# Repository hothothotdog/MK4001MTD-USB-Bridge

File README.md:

This repository has moved to [https://codeberg.org/hothothotdog/MK4001MTD-USB-Bridge](https://codeberg.org/hothothotdog/MK4001MTD-USB-Bridge)

This GitHub copy is a frozen archive. New commits, issues, and pull requests should go to Codeberg.

---

Budget friendly changes to the PCB. Modified the PCB from 4-layers and 11cm long (about $70) to under 10cm and 2-layers which puts this in the $5 cost range at jlcpcb 

Schematic changes:
   - TLV62569DBV 
   Filter caps changed to higher value (as per datasheet recommendation)
   Voltage divider changed from 112K 25.3K (3.2v out) to sensible values 270K 60K (3.33v out)
   - Leds
   Current limiters set to 1mA (plenty bright enough)
   - Crystal 12MHz
   Changed 27pf caps to correct capacitance of 10pF each
   - NOR Flash
   Changed part to correct winbond W25Q16JVUXIQ
   Package changed to the correct DFN 3x2mm 

   new kicad files uploaded (27-4-2026) + ibom + images + pdf
   
# MK4001MTD USB Bridge

**RP2040 Pico firmware that bridges a Toshiba MK4001MTD 0.85" SDIO microdrive as a USB Mass Storage device.**

The MK4001MTD is a 4 GB Microdrive originally used in the Nokia N91 music phone and some other devices, like MP3 players or USB drives, back when flash storage was still quite expensive.

You might have seen introductions claiming this drive uses the MMC protocol, but that’s actually incorrect. I’ve been investigating this for a while: I tried building an 8-bit MMCplus card reader and tested different SD/MMC readers without success. As a last resort, I bought a Nokia N91 to capture logic traces and confirm what protocol it actually uses.

Here is the photo when I was trying to use it with my 8bit-MMCPlus reader board, and it turns out it is not MMC :(

So I end up getting N91 to collect traces:

Unlike standard ATA/CF Microdrives, it uses an SDIO interface with ATA commands tunneled through CMD52/CMD53. No existing driver supports this protocol, so this firmware implements the full stack from scratch.

This surprised me, because there is an SDIO-to-ATA standard called CE-ATA. But if you look closely at the release timeline, CE-ATA came later than this drive. As a result, this drive relies entirely on SDIO commands, and CE-ATA is not available. CE-ATA has two new cmd CMD60/CMD61 and utilize CMD12/39, but you can see from the traces it is not using any of those.  

The second hardware point to mention is that another piece of misinformation floating around—claiming it’s an 8-bit MMCPlus card—is not only untrue, but the pinout doesn’t follow the MMC standard either. You can find the Nokia N91 service manual with some documentation on the pinout: while the pin numbering follows the MMCPlus standard, the pin mapping does not. This is an important detail if you’re wiring it yourself: it uses the same MMC connector, but the pin mapping is different, more in the Hardware section.

Finally, note that this is co-developed with Claude/OpenClaw. I collected the logic traces manually and set up a closed-loop test station for OpenClaw to iterate on development—analyzing the traces and implementing features. The documentation will mostly be written by Claude; I’ll add my notes inline as well. I’ve also read and double-checked the documentation myself, and it should be reliable and easy to follow.

For insights into the analytics on N91 trace, it is under /docs/N91_TRACE_ANALYSIS.md, I've also put the N91 service manual there along with the raw logic traces.

See more in the blog post here: [https://www.willwhang.dev/Reading-MK4001MTD/](https://www.willwhang.dev/Reading-MK4001MTD/)  
See it in activity here: [https://youtu.be/GC4xil3_Bbc](https://youtu.be/GC4xil3_Bbc)

## Status

Fully functional USB mass storage with PIO-accelerated reads/writes and idle power management.

| Metric | Value |
|--------|-------|
| Read speed | 550 kB/s |
| Write speed | 364 kB/s |
| Capacity | 3.75 GB (7,862,400 sectors) |
| Filesystem | FAT32 verified (mount/unmount/fsck clean) |
| Data integrity | Write+readback MD5 verified |
| Idle standby | 1 second timeout → STANDBY IMMEDIATE |

## How It Works

### Architecture

```
USB Host ←→ USB MSC (TinyUSB) ←→ ATA Layer ←→ SDIO Layer (PIO) ←→ MK4001MTD
```

The firmware has four layers:

1. **USB MSC** (`msc_device.c`) — TinyUSB Mass Storage Class. Translates SCSI READ(10)/WRITE(10) into ATA sector operations. EP buffer is 8192 bytes, batching up to 16 sectors per USB transfer. Activity LEDs on GP9 (TX/write) and GP10 (RX/read). Tracks last I/O timestamp for idle power management.

2. **ATA-over-SDIO** (`ata_sdio.c`) — Implements ATA commands (IDENTIFY, READ SECTORS, WRITE SECTORS) by writing to ATA registers mapped into SDIO function 1 address space via CMD52, and transferring sector data via CMD53. 3-tier retry logic at CMD, data, and ATA levels.

3. **PIO SDIO** (`sdio_pio.c`, `sdio.pio`) — Hardware-accelerated SDIO using RP2040's PIO peripheral. Three PIO programs share a single state machine via dynamic program swapping:
   - **CMD tx/rx** (26 instructions) — sends SDIO commands and receives responses
   - **DAT read** (13 instructions) — reads data blocks from 4-bit DAT bus via DMA
   - **DAT write** (16 instructions) — writes data blocks to 4-bit DAT bus via DMA, with built-in CRC status reception and busy-wait

4. **Bit-bang SDIO** (`sdio_hw.c`) — Software SDIO used only for card initialization at 400 KHz (before PIO is set up). All runtime I/O uses PIO.

Human notes: Interestingly, Claude was really reluctant to implement SDIO in PIO, and a lot of development cycles were wasted bouncing back and forth between PIO and bit-banging.

### The SDIO-ATA Protocol

The MK4001MTD presents itself as an SDIO card with one I/O function. Standard SDIO card initialization (CMD5/CMD3/CMD7) sets up the bus, then ATA registers are accessed through SDIO commands:

**Register access (CMD52):** Each ATA register is mapped to a function 1 address:

| Address | Register | Usage |
|---------|----------|-------|
| 0x00 | DATA | CMD53 target for sector data |
| 0x01 | ERR/FEAT | Error (read) / Feature (write) |
| 0x02 | SECCOUNT | Sector count |
| 0x03 | LBA_LO | LBA bits 0-7 |
| 0x04 | LBA_MID | LBA bits 8-15 |
| 0x05 | LBA_HI | LBA bits 16-23 |
| 0x06 | DEV/HEAD | Device/Head + LBA bits 24-27 |
| 0x07 | CMD/STATUS | Command (write) / Status (read) |

**Data transfer (CMD53):** Sector data is transferred by issuing CMD53 in block mode targeting the DATA register (address 0x00). For multi-sector reads, a single CMD53 with `block_count=N` transfers N × 512 bytes in one SDIO multi-block transaction.

**Interrupt signaling:** The drive signals sector readiness by asserting an SDIO interrupt (INT_PENDING bit 1 in CCCR register 0x05). Reading the ATA STATUS register clears the interrupt.

### Read Path (Multi-Block PIO)

For a 16-sector read:

```
1. Write ATA registers via PIO CMD52:
     SECCOUNT=16, LBA_LO/MID/HI, DEV/HEAD=0xE0, CMD=0x20

2. Poll STATUS via CMD52 until DRQ (bit 3) is set

3. Swap PIO to DAT read program
4. Send CMD53: block_mode=1, fn=1, addr=0x0000, block_count=16

5. PIO DAT read: for each of the 16 blocks:
   a. Wait for start bit (all DAT lines low)
   b. DMA 1024 nibbles (512 bytes) from PIO RX FIFO to buffer
   c. Wait for SM to finish clocking CRC+end nibbles (poll SM PC)
   d. Repack nibbles → bytes in-place

6. Swap PIO back to CMD program
```

### Write Path (Multi-Block PIO)

For a 16-sector write:

```
1. Write ATA registers via PIO CMD52:
     SECCOUNT=16, LBA, DEV/HEAD=0xE0, CMD=0x30

2. Poll STATUS via CMD52 until DRQ (bit 3) is set
   (STATUS 0xD8 = BSY+DRQ treated as DRQ-ready, per N91 trace)

3. Swap PIO to DAT write program
4. Send CMD53: block_mode=1, fn=1, addr=0x0000, block_count=16

5. PIO DAT write: for each of the 16 blocks:
   a. Precompute CRC16-CCITT per DAT line (4 independent CRCs)
   b. Build nibble stream: start(0x0) + data(1024 nibbles) + CRC(16) + end(0xF)
   c. DMA nibble stream to PIO TX FIFO
   d. PIO clocks out all nibbles, then:
      - Switches DAT to input
      - Clocks 16 cycles for CRC status from card
      - Polls DAT0 until card releases busy
      - Fires IRQ 0 to signal block completion

6. Swap PIO back to CMD program
```

### PIO Program Swapping

The RP2040 PIO has 32 instruction slots per block. Our three programs total 55 instructions, so they can't coexist. Instead, a single SM0 on PIO0 is used, and programs are swapped by writing directly to PIO instruction memory:

```c
static void load_program_raw(const pio_program_t *program) {
    for (uint i = 0; i < program->length; i++)
        pio->instr_mem[FIXED_OFFSET + i] = program->instructions[i];
}
```

This bypasses the SDK's `pio_add_program`/`pio_remove_program` allocator. Program swap takes ~1 µs. Each swap is followed by a program-specific reinit that sets pin mappings, shift direction, and clock divider.

### Power Management

Analysis of Nokia N91 logic traces reveals aggressive power management:

- **Idle mode:** STANDBY IMMEDIATE (0xE0) every **~7.5 seconds**, even with no I/O. Each standby triggers full SDIO re-initialization (CMD5 retry → CMD3 → CMD7 → CCCR setup). 28 standby cycles observed in one idle session.
- **Active mode:** Standby issued between bursts of I/O (24 cycles during USB drive file operations).
- No other power commands (IDLE, SLEEP, CHECK POWER MODE) or CCCR power register accesses observed.

The firmware replicates this behavior with a configurable idle timeout:

```c
#define IDLE_STANDBY_MS 5000  // in main.c
```

Two paths trigger HDD power gating:

1. **Idle timeout** (5 seconds) — main loop detects no I/O activity
2. **USB suspend** — host suspends the USB port

Both paths send ATA STANDBY IMMEDIATE (0xE0) to flush the write cache and park heads, then cut power via GP9.

**Wake sequence** (triggered by first READ/WRITE after gate):
1. Power on HDD, wait 500ms for rail settling
2. PIO-based SDIO reinit: CMD5 (OCR) → 10ms settle → CMD3 (RCA) → CMD7 (select)
3. Switch to fast PIO clock, configure CCCR via CMD52 (4-bit bus, 512B blocks, fn1 enable)
4. Poll fn1 ready (CCCR IO_READY bit 1)
5. N91-style 30ms DRDY status poll until drive is ATA-ready

### Bad Sector Handling

When a multi-sector transfer hits a bad sector:
1. Chunk read fails → error recovery (IO_ABORT + fn1 reset, ~500ms)
2. Falls back to per-sector I/O to identify the failing block precisely
3. The ATA layer waits long enough to capture the final `STATUS/ERROR` bits instead of collapsing the failure into a generic `DRQ timeout`
4. Bad sector LBA cached → subsequent access fails quickly without re-hammering the drive
5. Any unrecovered block fails the SCSI command immediately with `MEDIUM ERROR`

On the known failing root-directory sector (`LBA 1952`), the drive now reports the real ATA result:

```text
READ: ST=0x51 ERR ERR=0x40 UNC LBA=1952
FAST-RD: ST=0x51 ERR ERR=0x40 UNC LBA=1952
```

## Building

### Prerequisites

- Raspberry Pi Pico SDK
- ARM toolchain (`arm-none-eabi-gcc`)
- CMake

### Build & Flash

```bash
cd /home/pi/mk4001_bridge/build
cmake ..
make -j4

sudo openocd -f interface/cmsis-dap.cfg -f target/rp2040.cfg \
  -c "adapter speed 1000" -c "init" -c "reset halt" -c "sleep 200" \
  -c "program /home/pi/mk4001_bridge/build/mk4001_bridge.elf verify" \
  -c "reset run" -c "exit"
```

### Hardware Wiring

| Pico GPIO | Function | Notes |
|-----------|----------|-------|
| GP2 | SDIO_CLK | Host clock output |
| GP3 | SDIO_CMD | Bidirectional command line |
| GP4 | SDIO_DAT0 | Data bit 0 |
| GP5 | SDIO_DAT1 | Data bit 1 |
| GP6 | SDIO_DAT2 | Data bit 2 |
| GP7 | SDIO_DAT3 | Data bit 3 |
| GP9 | HDD_EN | Drive power enable (HIGH=on) |
| GP12 | UART TX | Debug output @ 115200 |
| GP13 | UART RX | Debug input |
| GP16 | LED: HDD Power | Active low |
| GP17 | LED: HDD Healthy | Active low |
| GP18 | LED: Read | Active low |
| GP19 | LED: Write | Active low |

**Note:** GP0 and GP1 are dead on this specific Pico unit. All SDIO pin assignments are shifted +2.

Human notes: Claude was wrong here because it didn’t realize that GP0 and GP1 were being used for the UART terminal in its build configuration. It kept forgetting this, to the point where I just moved the SDIO GPIOs off that UART.

HDD_PWR isn’t necessary. You don’t have to power-cycle the drive to use it; it’s more of a development convenience for resetting the HDD when a lot of things are hard-coded. That said, if you want power savings, you can use that signal, but it can handle warm reset without any issue.

You’ll see debug messages over UART. They’re not going through USB-CDC because it was easier for Claude to set up a separate UART-to-USB logging link that doesn’t disconnect or become unstable during early development.  
Here is a example of the log:

```
========================================
  MK4001MTD USB Bridge v0.11
  SDIO-ATA → USB Mass Storage (PIO)
========================================

[MAIN] Pre-delay 5000ms...
[PIO] Init OK: clkdiv=3.12 (~10.0 MHz), CMD@0
[MAIN] Power cycling HDD...
[SDIO] HDD power OFF
[SDIO] HDD power ON
[MAIN] SDIO init (PIO)...
[SDIO] CMD5 ready (OCR=0x901F8000)
[SDIO] RCA=0x0001
[SDIO] fn1 ready (attempt 0)
[MAIN] ATA IDENTIFY...
[ATA] IDENTIFY complete
Model:    [TOSHIBA MK4001MTD]
Serial:   [           763B004HA]
Firmware: [VH173A]
Sectors:  7862400 (3839 MB)
SMART:    not supported (supported=0, enabled=0)
IDENTIFY: W0=0040 W47=0000 W49=0000 W59=0000
  ATA W80=0000  Cmd W82=0000 W83=0000 W84=0000
  En  W85=0000 W86=0000 W87=0000  W89=0008 W128=0001

[DIAG] === Drive Diagnostics ===
[DIAG] Standard SMART: not supported (IDENTIFY W82 bit0 = 0)
[DIAG] Toshiba vendor CMD 0xC2:
  FEAT=0x01 unknown_01                       → SC=00 LBA=02/00/00 ST=50
  FEAT=0x02 unknown_02                       â SC=00 LBA=02/00/00 ST=50
  FEAT=0x03 unknown_03                       → SC=00 LBA=02/00/00 ST=50
  FEAT=0x04 unknown_04                       → SC=00 LBA=02/00/00 ST=50
  FEAT=0x10 diag_10 (LBA_LO varies)          → SC=00 LBA=00/00/00 ST=50
  FEAT=0x11 diag_11                          → SC=00 LBA=00/00/00 ST=50
  FEAT=0x12 diag_12 (LBA_LO varies)          → SC=00 LBA=01/00/00 ST=50
  FEAT=0x20 query_20 (N91: SC=0xFF always)   → SC=FE LBA=00/FF/00 ST=50
  FEAT=0x21 query_21 (N91: SC varies per boot) → SC=1B LBA=00/FF/00 ST=50

[MAIN] MBR: valid 0x55AA
[MAIN] Warming up...
[MAIN] PIO OK, STATUS=0x50
[MAIN] Drive: 7862400 sectors (3839 MB)
[MAIN] Ready.
[PWR] Idle 5000ms → STANDBY + power gate
[PWR] STANDBY IMMEDIATE → power gate
[SDIO] HDD power OFF
```

Finally, here’s the wiring to the actual drive.  

Here is a crop from the N91 schematic, you can map the pin number also.

Side note that this is a 3V drive but I think 3.3V is fine, mostly it is to save some level shifting work.  

HW specifically designed for this drive is under /hardware!

## Source Files

| File | Lines | Purpose |
|------|-------|---------|
| `main.c` | 210 | Init, idle standby, USB suspend/resume |
| `msc_device.c` | 400 | USB MSC callbacks, power gate wake, bad sector cache |
| `ata_sdio.c` | 390 | ATA commands, error recovery, vendor diagnostics |
| `sdio_pio.c` | 635 | PIO SDIO: CMD52, CMD53 read/write, program swap, CRC16 |
| `sdio_hw.c` | 45 | Pin init + HDD power control |
| `sdio.pio` | 200 | PIO assembly + C SDK init helpers |
| `led.h` | 37 | LED helpers (GP16–GP19, active low) |
| `usb_descriptors.c` | 77 | USB device/config/string descriptors |
| `tusb_config.h` | 20 | TinyUSB config (MSC, 32KB EP buffer) |

## Version History

| Version | Read | Write | Key Change |
|---------|------|-------|------------|
| v0.1–v0.3 | 105 kB/s | 93 kB/s | Bit-bang SDIO, CRC16, retry logic |
| v0.5 | 374 kB/s | — | Single-SM PIO, direct instruction memory swap |
| v0.6 | 583 kB/s | 93 kB/s | Multi-block CMD53 reads, CRC clock drain fix |
| v0.8 | 588 kB/s | 274 kB/s | PIO writes, OSR flush fix |
| v0.9 | 475 kB/s | 371 kB/s | 64-sector chunks, CRC16 read verification |
| v0.10 | 453 kB/s | 329 kB/s | LED remap, HDD EN pin, UART on GP12/GP13 |
| **v0.11** | **~450 kB/s** | **~340 kB/s** | **HDD power gate, PIO wake, bad sector sense, USB suspend** |

## Testing

```bash
# Check device appeared
lsblk -dno NAME,MODEL | grep MK4001

# Filesystem test — mount, copy files, verify
sudo mount /dev/sdX1 /mnt/mk4001
cp /tmp/testfile /mnt/mk4001/
sync
md5sum /tmp/testfile /mnt/mk4001/testfile    # should match
sudo umount /mnt/mk4001

# Speed benchmarks (raw device, do NOT mount first — will corrupt filesystem)
# Use a safe offset past the filesystem or an unpartitioned drive
sudo dd if=/dev/sdX of=/dev/null bs=64k count=128 iflag=direct     # read
sudo dd if=/dev/zero of=/dev/sdX bs=64k count=64 oflag=direct seek=1024  # write (offset past FS)
```

Human notes here, fun fact: When it first starts to do speed testing, it actually dd directly to the drive and damage the filesystems..... Thankfully it doesn't matter that much here during the developments but always keep in mind when you handle OpenClaw your setup.

## License

I don't care.

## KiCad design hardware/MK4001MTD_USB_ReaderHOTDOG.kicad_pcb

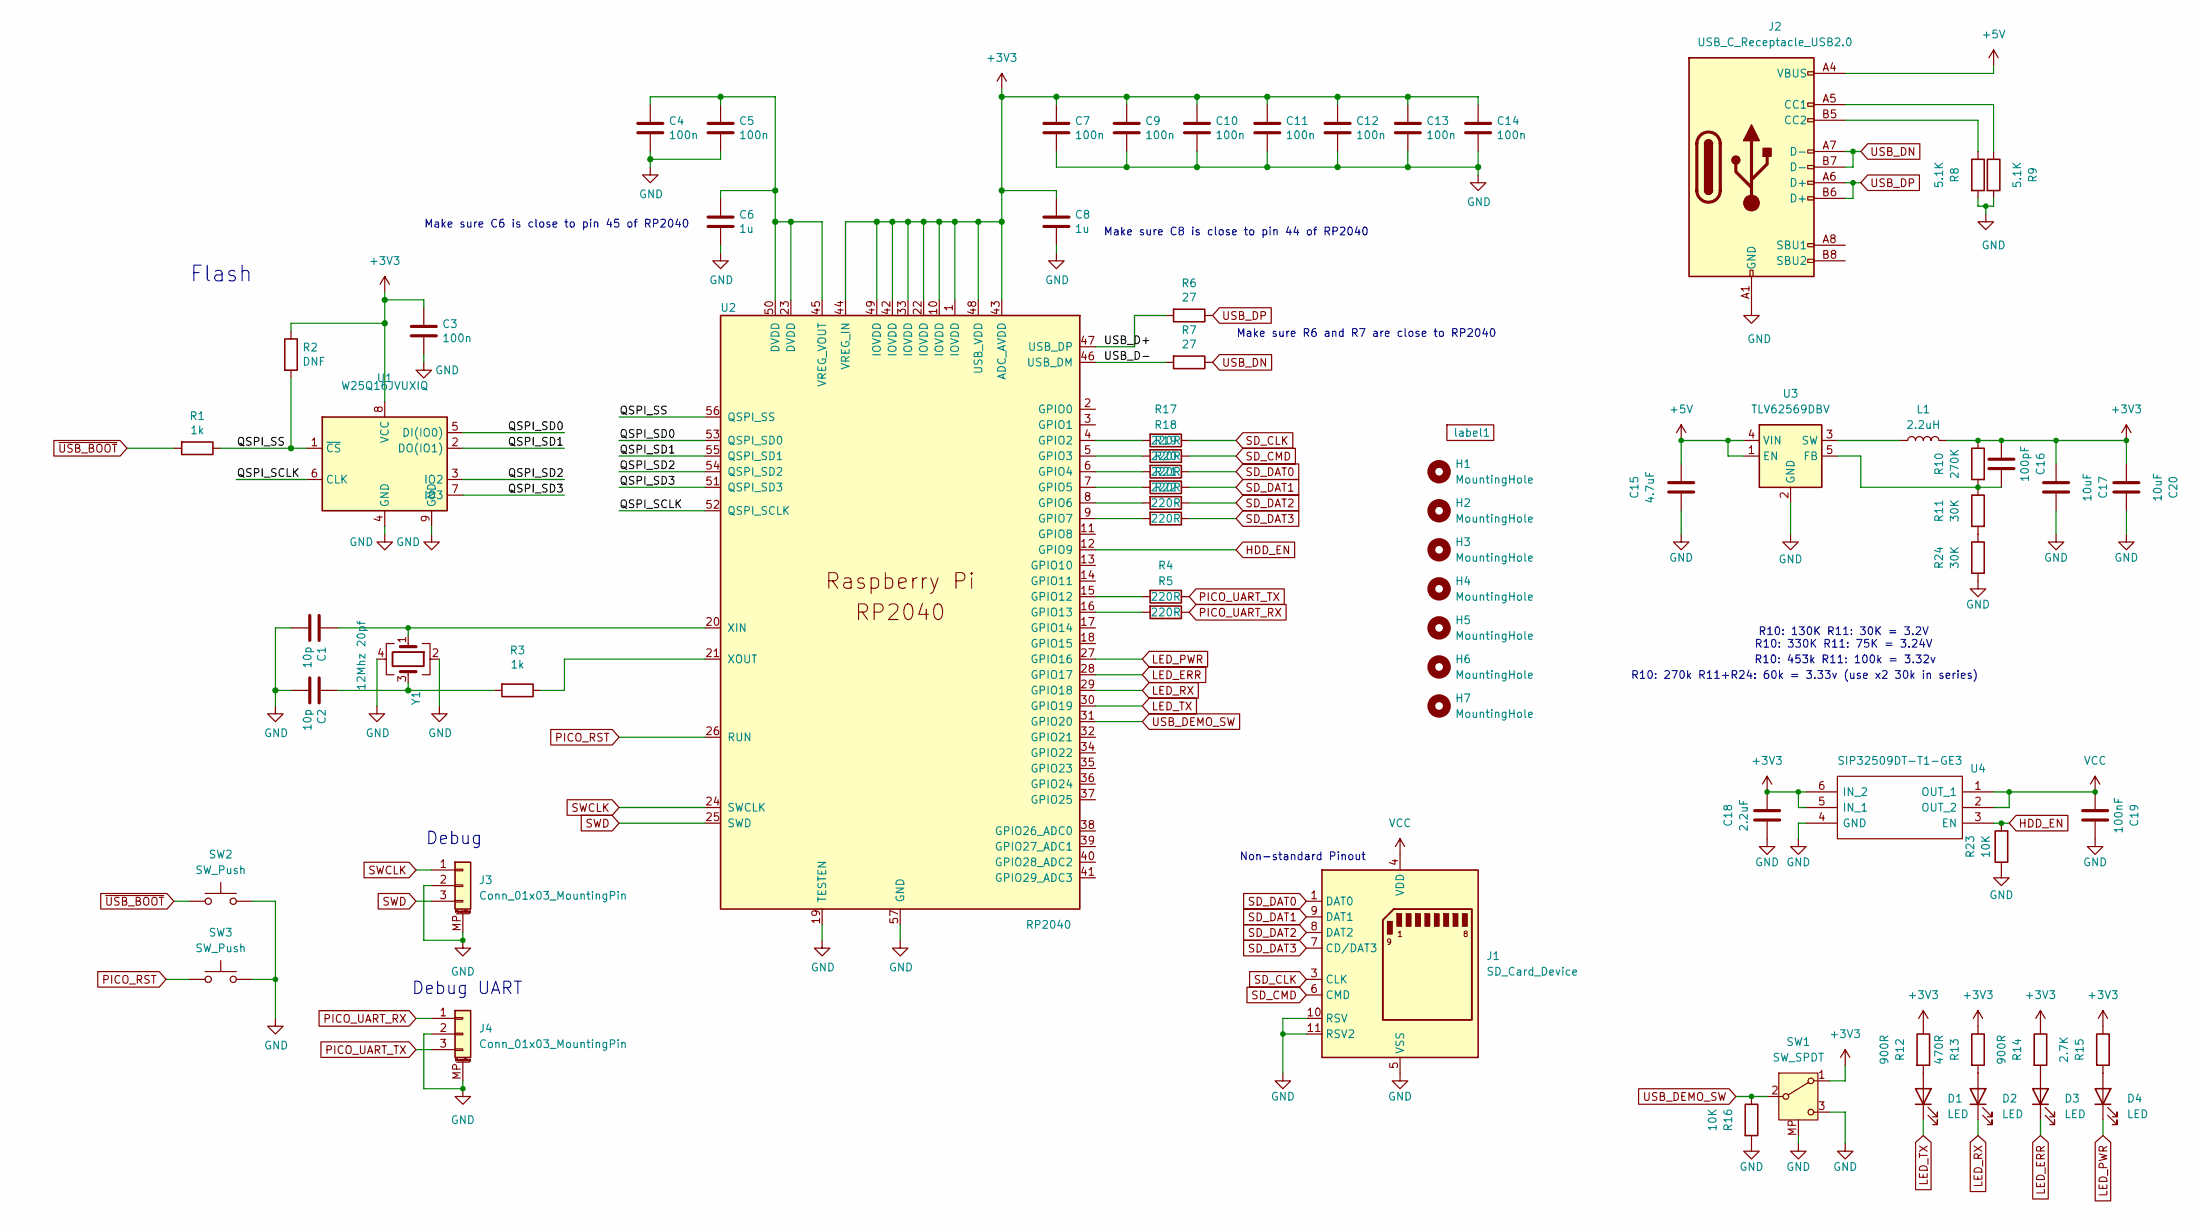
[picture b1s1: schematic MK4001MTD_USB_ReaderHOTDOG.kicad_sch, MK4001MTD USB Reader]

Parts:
C1, C2: 10p; C_0402_1005Metric
C3, C4, C5, C7, C9, C10, C11, C12, C13, C14: 100n; C_0402_1005Metric
C6, C8: 1u; C_0402_1005Metric
C15: 4.7uF; C_0805_2012Metric
C16: 100pF; C_0402_1005Metric
C17, C20: 10uF; C_0805_2012Metric
C18: 2.2uF; C_0805_2012Metric
C19: 100nF; C_0402_1005Metric
D1, D2, D3, D4: LED; LED_0603_1608Metric
H1, H2, H3, H4, H5, H6, H7: MountingHole; MountingHole_2.2mm_M2
J1: SD_Card_Device; MK4001MTD
J2: USB_C_Receptacle_USB2.0; USB_C_Receptacle_XKB_U262-16XN-4BVC11
J3, J4: Conn_01x03_MountingPin; JST_SH_SM03B-SRSS-TB_1x03-1MP_P1.00mm_Horizontal
L1: 2.2uH; L_Vishay_IHLP-2020
R1, R3: 1k; R_0402_1005Metric
R2: DNF; R_0402_1005Metric
R4, R5, R17, R18, R19, R20, R21, R22: 220R; R_0402_1005Metric
R6, R7: 27; R_0402_1005Metric
R8, R9: 5.1K; R_0402_1005Metric
R10: 270K; R_0402_1005Metric
R11, R24: 30K; R_0402_1005Metric
R12, R14: 900R; R_0402_1005Metric
R13: 470R; R_0402_1005Metric
R15: 2.7K; R_0402_1005Metric
R16, R23: 10K; R_0402_1005Metric
SW1: SW_SPDT; SW_SPDT_PCM12
SW2, SW3: SW_Push; SW_Tactile_SPST_NO_Straight_CK_PTS636Sx25SMTRLFS
U1: W25Q16JVUXIQ; Winbond_USON-8-1EP_3x2mm_P0.5mm_EP0.2x1.6mm
U2: RP2040; RP2040-QFN-56
U3: TLV62569DBV; SOT-23-5
U4: SIP32509DT-T1-GE3; SOT-23-6; Mouser Part Number 78-SIP32509DT-T1-GE3
Y1: 12Mhz 20pf; Crystal_SMD_3225-4Pin_3.2x2.5mm
label1: QRCode

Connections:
+3V3: C3.1, C7.1, C8.1, C9.1, C10.1, C11.1, C12.1, C13.1, C14.1, C16.1, C17.1, C18.2, C20.1, L1.2, R2.1, R10.1, R12.1, R13.1, R14.1, R15.1, SW1.1 (A), U1.8 (VCC), U2.1 (IOVDD), U2.10 (IOVDD), U2.22 (IOVDD), U2.33 (IOVDD), U2.42 (IOVDD), U2.43 (ADC_AVDD), U2.44 (VREG_IN), U2.48 (USB_VDD), U2.49 (IOVDD), U4.5 (IN_1), U4.6 (IN_2)
+5V: C15.2, J2.A4 (VBUS), J2.A9 (VBUS), J2.B4 (VBUS), J2.B9 (VBUS), U3.1 (EN), U3.4 (VIN)
/QSPI_SCLK: U1.6 (CLK), U2.52 (QSPI_SCLK)
/QSPI_SD0: U1.5 (DI(IO0)), U2.53 (QSPI_SD0)
/QSPI_SD1: U1.2 (DO(IO1)), U2.55 (QSPI_SD1)
/QSPI_SD2: U1.3 (IO2), U2.54 (QSPI_SD2)
/QSPI_SD3: U1.7 (IO3), U2.51 (QSPI_SD3)
/QSPI_SS: R1.1, R2.2, U1.1 (~CS), U2.56 (QSPI_SS)
/USB_D+: R6.2, U2.47 (USB_DP)
/USB_D-: R7.2, U2.46 (USB_DM)
GND: C1.2, C2.2, C3.2, C4.2, C5.2, C6.2, C7.2, C8.2, C9.2, C10.2, C11.2, C12.2, C13.2, C14.2, C15.1, C17.2, C18.1, C19.2, C20.2, J1.2 (VSS), J1.5 (VSS), J1.10 (RSV), J1.11 (RSV2), J2.A1 (GND), J2.A12 (GND), J2.B1 (GND), J2.B12 (GND), J3.2, J3.MP (MountPin), J4.2, J4.MP (MountPin), R8.2, R9.2, R16.2, R23.1, R24.2, SW1.3 (C), SW1.MP, SW2.2, SW3.2, U1.4 (GND), U1.9 (GND), U2.19 (TESTEN), U2.57 (GND), U3.2 (GND), U4.4 (GND), Y1.2, Y1.4
HDD_EN: R23.2, U2.12 (GPIO9), U4.3 (EN)
LED_ERR: D3.1 (K), U2.28 (GPIO17)
LED_PWR: D4.1 (K), U2.27 (GPIO16)
LED_RX: D2.1 (K), U2.29 (GPIO18)
LED_TX: D1.1 (K), U2.30 (GPIO19)
unnamed: C2.1, R3.2, Y1.3
unnamed: D1.2 (A), R12.2
unnamed: D2.2 (A), R13.2
unnamed: D3.2 (A), R14.2
unnamed: D4.2 (A), R15.2
unnamed: J2.A5 (CC1), R9.1
unnamed: J2.B5 (CC2), R8.1
unnamed: R11.2, R24.1
unnamed: R17.2, U2.4 (GPIO2)
unnamed: R18.2, U2.5 (GPIO3)
unnamed: R19.2, U2.6 (GPIO4)
unnamed: R20.2, U2.7 (GPIO5)
unnamed: R21.2, U2.8 (GPIO6)
unnamed: R22.2, U2.9 (GPIO7)
unnamed: R4.2, U2.15 (GPIO12)
unnamed: R5.2, U2.16 (GPIO13)
unnamed: C4.1, C5.1, C6.1, U2.23 (DVDD), U2.45 (VREG_VOUT), U2.50 (DVDD)
unnamed: C1.1, U2.20 (XIN), Y1.1
unnamed: R3.1, U2.21 (XOUT)
unnamed: C16.2, R10.2, R11.1, U3.5 (FB)
unnamed: L1.1, U3.3 (SW)
PICO_RST: SW3.1, U2.26 (RUN)
PICO_UART_RX: J4.1, R5.1
PICO_UART_TX: J4.3, R4.1
SD_CLK: J1.3 (CLK), R17.1
SD_CMD: J1.6 (CMD), R18.1
SD_DAT0: J1.1 (DAT0), R19.1
SD_DAT1: J1.9 (DAT1), R20.1
SD_DAT2: J1.8 (DAT2), R21.1
SD_DAT3: J1.7 (CD/DAT3), R22.1
SWCLK: J3.1, U2.24 (SWCLK)
SWD: J3.3, U2.25 (SWD)
USB_DEMO_SW: R16.1, SW1.2 (B), U2.31 (GPIO20)
USB_DN: J2.A7 (D-), J2.B7 (D-), R7.1
USB_DP: J2.A6 (D+), J2.B6 (D+), R6.1
VCC: C19.1, J1.4 (VDD), U4.1 (OUT_1), U4.2 (OUT_2)
~USB_BOOT: R1.2, SW2.1

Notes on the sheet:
R10: 453k R11: 100k = 3.32v
Debug UART
Make sure R6 and R7 are close to RP2040
Flash
Make sure C8 is close to pin 44 of RP2040
R10: 270k R11+R24: 60k = 3.33v (use x2 30k in series)
Debug
R10: 130K R11: 30K = 3.2V R10: 330K R11: 75K = 3.24V
Make sure C6 is close to pin 45 of RP2040
Non-standard Pinout

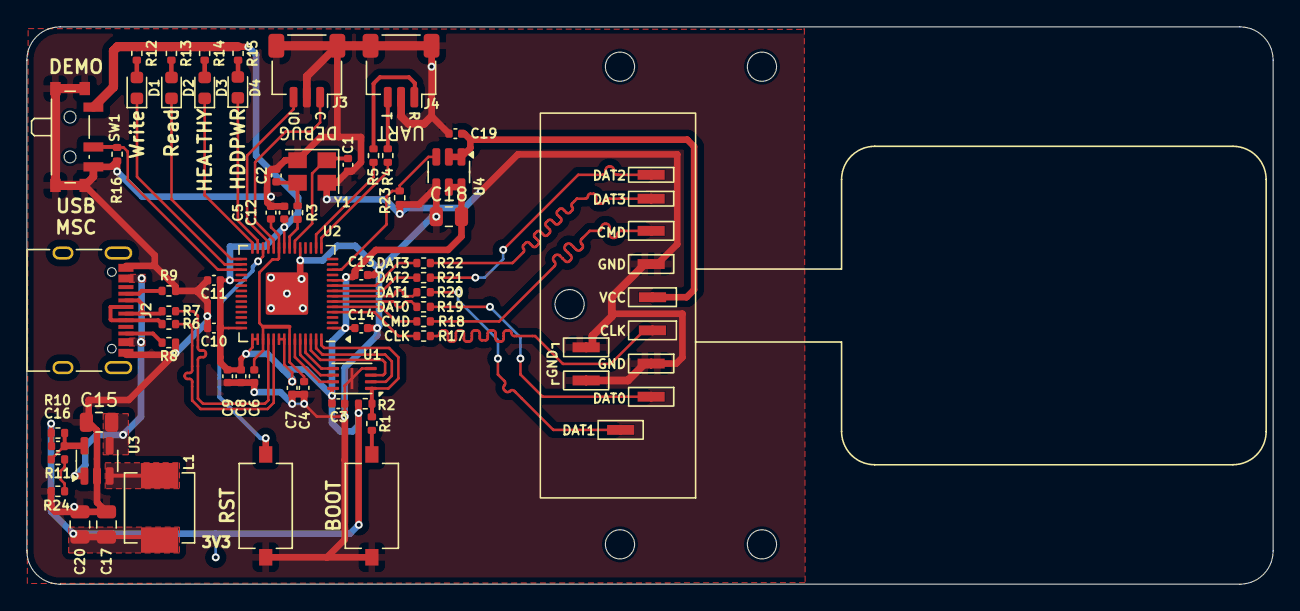
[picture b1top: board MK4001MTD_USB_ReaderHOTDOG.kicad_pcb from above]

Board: 2 copper layers, 93.9 x 42.0 mm, 66 parts (0 on the bottom side), 53 nets.

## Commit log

2026-03-01 Adding debug log output
2026-03-01 Update README with notes on dd command usage
    Added human notes about dd command usage and potential risks.
2026-03-16 Add image of MK4001MTD reader to README
    Added an image of the MK4001MTD reader to the README.
2026-03-16 Revise log example for MK4001MTD USB Bridge
    Updated log example with new version details and improved formatting.
2026-04-27 Project updated for all changes
2026-04-27 Update BOM for all changes
2026-04-27 Updated PCB
2026-04-27 Updated Gerbers
2026-04-27 Updated schematic
2026-04-27 Updates and zones
2026-04-27 u[dated pcb and zones
